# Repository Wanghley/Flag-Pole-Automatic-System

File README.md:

<!-- Improved compatibility of back to top link: See: https://github.com/othneildrew/Best-README-Template/pull/73 -->

<!--
*** Thanks for checking out the Best-README-Template. If you have a suggestion
*** that would make this better, please fork the repo and create a pull request
*** or simply open an issue with the tag "enhancement".
*** Don't forget to give the project a star!
*** Thanks again! Now go create something AMAZING! :D
-->

<!-- PROJECT SHIELDS -->
<!--
*** I'm using markdown "reference style" links for readability.
*** Reference links are enclosed in brackets [ ] instead of parentheses ( ).
*** See the bottom of this document for the declaration of the reference variables
*** for contributors-url, forks-url, etc. This is an optional, concise syntax you may use.
*** https://www.markdownguide.org/basic-syntax/#reference-style-links
-->
[![Contributors][contributors-shield]][contributors-url]
[![Forks][forks-shield]][forks-url]
[![Stargazers][stars-shield]][stars-url]
[![Issues][issues-shield]][issues-url]
[![MIT License][license-shield]][license-url]
[![LinkedIn][linkedin-shield]][linkedin-url]

<!-- PROJECT LOGO -->
<br />
<div align="center">

  <h3 align="center">Remotely Controlled Flag-Hoisting Device</h3>

  <p align="center">
    Revolutionizing the way any institution hoists its flags! Our team of aspirant engineers at the Duke Pratt School of Engineering have designed a cutting-edge, remotely controlled flag-raising system that eliminates the need for manual labor and reduces costs for the university. With our innovative technology, flag heights can be adjusted safely and easily from any location with Wi-Fi access, making it a reliable and affordable solution. Say goodbye to labor costs and health risks associated with manual flag hoisting and hello to efficient and automated flag-raising with our state-of-the-art system!
    <br />
    <a href="https://github.com/Wanghley/Flag-Pole-Automatic-System"><strong>Explore the docs »</strong></a>
    <br />
    <br />
    <a href="https://github.com/Wanghley/Flag-Pole-Automatic-System">View Demo</a>
    ·
    <a href="https://github.com/Wanghley/Flag-Pole-Automatic-System/issues">Report Bug</a>
    ·
    <a href="https://github.com/Wanghley/Flag-Pole-Automatic-System/issues">Request Feature</a>
  </p>
</div>

<!-- TABLE OF CONTENTS -->
<details>
  <summary>Table of Contents</summary>
  <ol>
    <li>
      <a href="#about-the-project">About The Project</a>
      <ul>
        <li><a href="#built-with">Built With</a></li>
      </ul>
    </li>
    <li>
      <a href="#getting-started">Getting Started</a>
      <ul>
        <li><a href="#prerequisites">Prerequisites</a></li>
        <li><a href="#installation">Installation</a></li>
      </ul>
    </li>
    <li><a href="#usage">Usage</a></li>
    <li><a href="#roadmap">Roadmap</a></li>
    <li><a href="#contributing">Contributing</a></li>
    <li><a href="#license">License</a></li>
    <li><a href="#contact">Contact</a></li>
    <li><a href="#acknowledgments">Acknowledgments</a></li>
  </ol>
</details>

<!-- ABOUT THE PROJECT -->
## About The Project

[![Product Name Screen Shot][product-screenshot]](https://example.com)

We built a remotely controlled, automatic, flag-hoisting device to service Duke University. Our client, Lee Clayton, a locksmithing specialist at Duke, has tasked us with creating an automatic, remotely-controlled system to more efficiently change flag heights for holidays and current events that require half-masting. When these special occasions arise, Duke currently relies on manual labor to lower or raise each flag one at a time.

This current system is suboptimal due to:

- Adverse weather conditions that prohibit access to flags
- Long walking time to all 16 flag poles around Duke’s campuses
- Each trip costs Duke $250 dollars, totaling to over $50,000 in the last decade.
- At the moment, the market only has automated machines that are attached to the flagpole with no remote control, an inadequate solution for the client as someone would still need to visit each pole. Our solution allows for remote control from any location with access to Duke Wi-Fi.

<p align="right">(<a href="#readme-top">back to top</a>)</p>

### Built With

<p align="right">(<a href="#readme-top">back to top</a>)</p>

<!-- GETTING STARTED -->
## Getting Started

This is an example of how you may give instructions on setting up your project locally.
To get a local copy up and running follow these simple example steps.

### Prerequisites

This is an example of how to list things you need to use the software and how to install them.
* npm
  ```sh
  npm install npm@latest -g
  ```

### Installation

_Below is an example of how you can instruct your audience on installing and setting up your app. This template doesn't rely on any external dependencies or services._

1. Get a free API Key at [https://example.com](https://example.com)
2. Clone the repo
   ```sh
   git clone https://github.com/your_username_/Project-Name.git
   ```
3. Install NPM packages
   ```sh
   npm install
   ```
4. Enter your API in `config.js`
   ```js
   const API_KEY = 'ENTER YOUR API';
   ```

<p align="right">(<a href="#readme-top">back to top</a>)</p>

<!-- USAGE EXAMPLES -->
## Usage

Use this space to show useful examples of how a project can be used. Additional screenshots, code examples and demos work well in this space. You may also link to more resources.

_For more examples, please refer to the [Documentation](https://example.com)_

<p align="right">(<a href="#readme-top">back to top</a>)</p>

<!-- ROADMAP -->
## Roadmap

- [x] Add Changelog
- [x] Add back to top links
- [ ] Add Additional Templates w/ Examples
- [ ] Add "components" document to easily copy & paste sections of the readme
- [ ] Multi-language Support
    - [ ] Chinese
    - [ ] Spanish

See the [open issues](https://github.com/othneildrew/Best-README-Template/issues) for a full list of proposed features (and known issues).

<p align="right">(<a href="#readme-top">back to top</a>)</p>

<!-- CONTRIBUTING -->
## Contributing

Contributions are what make the open source community such an amazing place to learn, inspire, and create. Any contributions you make are **greatly appreciated**.

If you have a suggestion that would make this better, please fork the repo and create a pull request. You can also simply open an issue with the tag "enhancement".
Don't forget to give the project a star! Thanks again!

1. Fork the Project
2. Create your Feature Branch (`git checkout -b feature/AmazingFeature`)
3. Commit your Changes (`git commit -m 'Add some AmazingFeature'`)
4. Push to the Branch (`git push origin feature/AmazingFeature`)
5. Open a Pull Request

<p align="right">(<a href="#readme-top">back to top</a>)</p>

<!-- LICENSE -->
## License

Distributed under the MIT License. See `LICENSE.txt` for more information.

<p align="right">(<a href="#readme-top">back to top</a>)</p>

<!-- CONTACT -->
## Contact

Your Name - [@your_twitter](https://twitter.com/your_username) - email@example.com

Project Link: [https://github.com/your_username/repo_name](https://github.com/your_username/repo_name)

<p align="right">(<a href="#readme-top">back to top</a>)</p>

<!-- ACKNOWLEDGMENTS -->
## Acknowledgments

Use this space to list resources you find helpful and would like to give credit to. I've included a few of my favorites to kick things off!

* [Choose an Open Source License](https://choosealicense.com)
* [GitHub Emoji Cheat Sheet](https://www.webpagefx.com/tools/emoji-cheat-sheet)
* [Malven's Flexbox Cheatsheet](https://flexbox.malven.co/)
* [Malven's Grid Cheatsheet](https://grid.malven.co/)
* [Img Shields](https://shields.io)
* [GitHub Pages](https://pages.github.com)
* [Font Awesome](https://fontawesome.com)
* [React Icons](https://react-icons.github.io/react-icons/search)

<p align="right">(<a href="#readme-top">back to top</a>)</p>

<!-- MARKDOWN LINKS & IMAGES -->
<!-- https://www.markdownguide.org/basic-syntax/#reference-style-links -->
[contributors-shield]: https://img.shields.io/github/contributors/Wanghley/Flag-Pole-Automatic-System.svg?style=for-the-badge
[contributors-url]: https://github.com/Wanghley/Flag-Pole-Automatic-System/graphs/contributors
[forks-shield]: https://img.shields.io/github/forks/Wanghley/Flag-Pole-Automatic-System.svg?style=for-the-badge
[forks-url]: https://github.com/Wanghley/Flag-Pole-Automatic-System/network/members
[stars-shield]: https://img.shields.io/github/stars/Wanghley/Flag-Pole-Automatic-System.svg?style=for-the-badge
[stars-url]: https://github.com/Wanghley/Flag-Pole-Automatic-System/stargazers
[issues-shield]: https://img.shields.io/github/issues/Wanghley/Flag-Pole-Automatic-System.svg?style=for-the-badge
[issues-url]: https://github.com/Wanghley/Flag-Pole-Automatic-System/issues
[license-shield]: https://img.shields.io/github/license/Wanghley/Flag-Pole-Automatic-System.svg?style=for-the-badge
[license-url]: https://github.com/Wanghley/Flag-Pole-Automatic-System/blob/master/LICENSE.md
[linkedin-shield]: https://img.shields.io/badge/-LinkedIn-black.svg?style=for-the-badge&logo=linkedin&colorB=555
[linkedin-url]: https://linkedin.com/in/wanghley
[product-screenshot]: images/screenshot.png
[Next.js]: https://img.shields.io/badge/next.js-000000?style=for-the-badge&logo=nextdotjs&logoColor=white
[Next-url]: https://nextjs.org/
[React.js]: https://img.shields.io/badge/React-20232A?style=for-the-badge&logo=react&logoColor=61DAFB
[React-url]: https://reactjs.org/
[Vue.js]: https://img.shields.io/badge/Vue.js-35495E?style=for-the-badge&logo=vuedotjs&logoColor=4FC08D
[Vue-url]: https://vuejs.org/
[Angular.io]: https://img.shields.io/badge/Angular-DD0031?style=for-the-badge&logo=angular&logoColor=white
[Angular-url]: https://angular.io/
[Svelte.dev]: https://img.shields.io/badge/Svelte-4A4A55?style=for-the-badge&logo=svelte&logoColor=FF3E00
[Svelte-url]: https://svelte.dev/
[Laravel.com]: https://img.shields.io/badge/Laravel-FF2D20?style=for-the-badge&logo=laravel&logoColor=white
[Laravel-url]: https://laravel.com
[Bootstrap.com]: https://img.shields.io/badge/Bootstrap-563D7C?style=for-the-badge&logo=bootstrap&logoColor=white
[Bootstrap-url]: https://getbootstrap.com
[JQuery.com]: https://img.shields.io/badge/jQuery-0769AD?style=for-the-badge&logo=jquery&logoColor=white
[JQuery-url]: https://jquery.com

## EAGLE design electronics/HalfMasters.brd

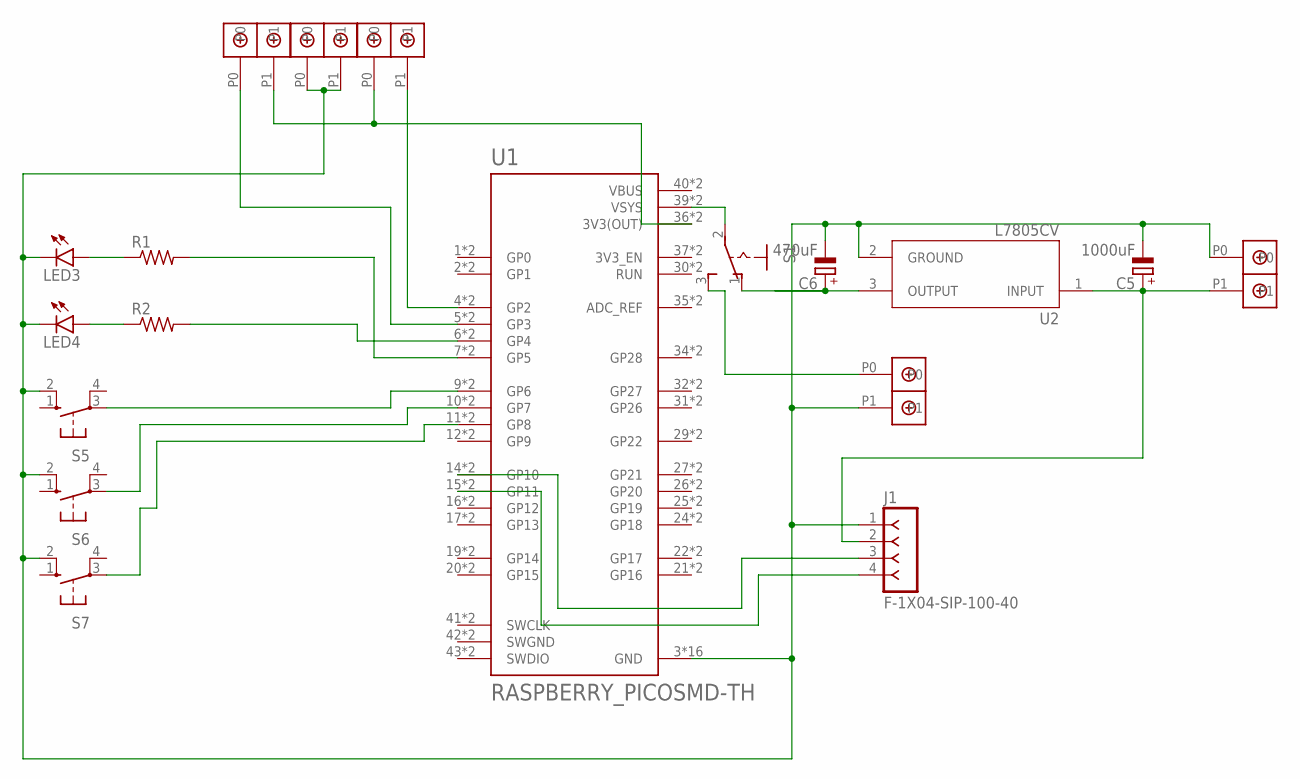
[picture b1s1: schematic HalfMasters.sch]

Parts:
C5: 1000uF; E2-5
C6: 470uF; E2-5
J1: F-1X04-SIP-100-40; SIP-100-04-40
LED3, LED4: LED5MM
R1, R2: R-US_0207/10; 0207/10
S1: 255SB
S5, S6, S7: 10-XX; B3F-10XX
U1: RASPBERRY_PICOSMD-TH; PICO-PKG
U2: L7805CV; TO255P1040X460X1968-3
U$1, U$2, U$3, U$4, U$5: DBCONN-1X2

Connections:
unnamed: R2.2, U1.6 (GP4), U1.P$6 (GP4)
unnamed: R1.2, U1.7 (GP5), U1.P$7 (GP5)
unnamed: S1.3 (S), U$5.P0
unnamed: J1.3, U1.14 (GP10), U1.P$14 (GP10)
unnamed: J1.4, U1.15 (GP11), U1.P$15 (GP11)
unnamed: S1.2, U1.39 (VSYS), U1.P$39 (VSYS)
unnamed: C6.+, S1.1 (O), U2.3 (OUTPUT)
unnamed: U1.36 (3V3(OUT)), U1.P$36 (3V3(OUT)), U$1.P1, U$3.P0
unnamed: U1.4 (GP2), U1.P$4 (GP2), U$3.P1
unnamed: U1.5 (GP3), U1.P$5 (GP3), U$1.P0
unnamed: LED3.A, R1.1
unnamed: LED4.A, R2.1
unnamed: C5.+, J1.2, U2.1 (INPUT), U$4.P1
unnamed: C5.-, C6.-, J1.1, LED3.K (C), LED4.K (C), S5.2 (S1), S6.2 (S1), S7.2 (S1), U1.3 (GND), U1.8 (GND), U1.13 (GND), U1.18 (GND), U1.23 (GND), U1.28 (GND), U1.33 (GND), U1.38 (GND), U1.P$3 (GND), U1.P$8 (GND), U1.P$13 (GND), U1.P$18 (GND), U1.P$23 (GND), U1.P$28 (GND), U1.P$33 (GND), U1.P$38 (GND), U2.2 (GROUND), U$2.P0, U$2.P1, U$4.P0, U$5.P1
unnamed: S5.3, U1.9 (GP6), U1.P$9 (GP6)
unnamed: S6.3, U1.10 (GP7), U1.P$10 (GP7)
unnamed: S7.3, U1.11 (GP8), U1.P$11 (GP8)
SWGND: U1.42 (SWGND), U1.P$42 (SWGND)
VBUS: U1.40 (VBUS), U1.P$40 (VBUS)

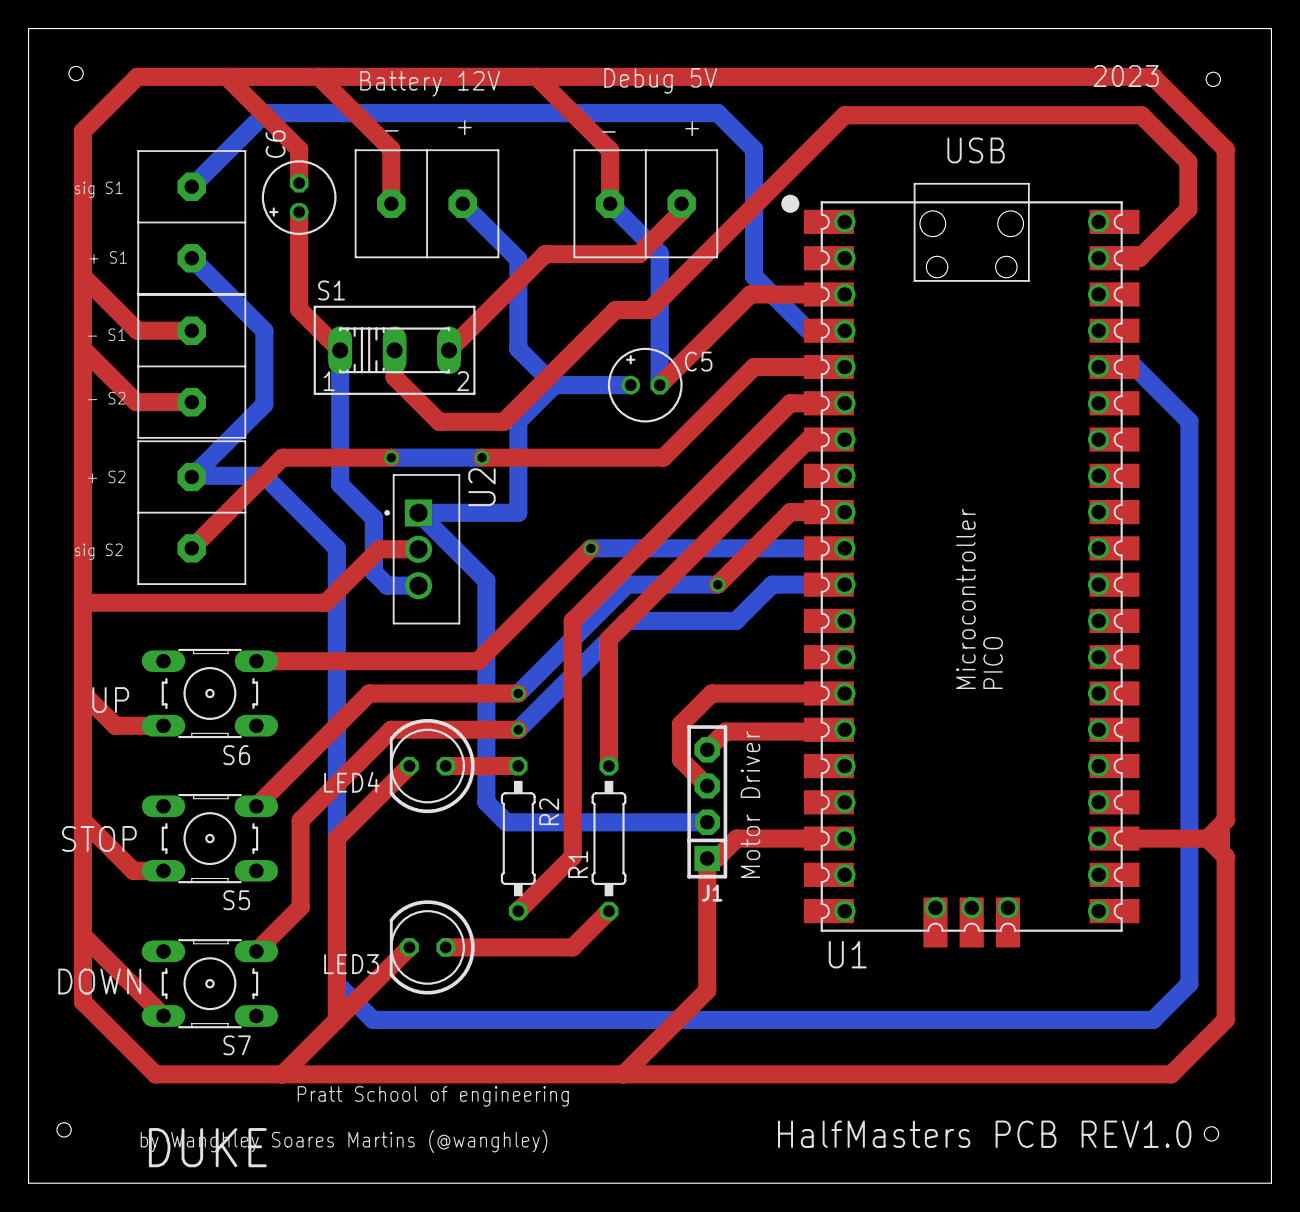
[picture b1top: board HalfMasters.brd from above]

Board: 2 copper layers, 87.0 x 80.8 mm, 18 parts (0 on the bottom side), 19 nets.

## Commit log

2022-10-19 feat: initial work on README for flagpole project
    Add initial template to work on for the flag pole project
2022-10-19 feat: functional firmware for prototype using angular movement
2022-10-24 feat: insert automatic command to set up and down
2022-10-24 feat: full control of motion of the device
    TODO: needs to implement saving on EEPROM and set up remote control by IP address
2022-10-26 fix!: correct movement from top position to middle position
    Wrong movement command on moving from up to middle corrected
2022-10-26 fix: remove non-used variables
    remove variables not used in the context what of problem
2022-10-26 feat!: implements EEPROM storage and data recovery
    Implements writting and reading on the EEPROM
2022-11-16 fix!: operational microcontroller kit functional w serial communication
    implemented communication to be received from nodemcu through wireless
2022-11-16 feat: nodeMCU ESP8266 rest API functional code + serial comm
    Implements ESP8266 rest API w/ Serial communication to microcontroller
2022-11-21 feat: implementation NEMA 23 + AccelStepper
    Implement AccelStepper library v1.61.0
    Default setings for NEMA 23 motor driver
    TB6600
2023-01-28 commit1
2023-01-28 refactor: move website and api code to web folder
2023-02-12 feat: initial code developed for pico W implementation
2023-02-12 feat: implementation with microdot
    add initial page
    add initial work on go up and down
    implement async webserver
2023-02-12 feat: add more information to / page
2023-02-16 feat: initial addiction of libraries and electronics folder to repository
2023-03-20 feat: libraries for new components of motor drive added
2023-03-20 feat: electronics libraries added
2023-03-20 feat: initial functional code with pico platform
    functional code with basic implementation on the raspberry pi
    Only one hall effect sensor added
2023-03-20 feat: database schema and design
    first draw of the database for the project
2023-03-20 feat: initial work on SQL for the database - written based on the schema
2023-03-22 fix!: add cardinality to MER diagram
    DB version one ready to be programmed and deployed to website.
2023-03-23 feat: final rev 1 schematic of controller circuit
2023-03-23 feat: rev 1 of the PCB designed ready
2023-03-23 refactor: logo for PCB
2023-03-23 refactor: schematic needed libraries
2023-03-23 fix: add correct attributes and mapping
2023-03-24 fix: change vias width to match Duke requirements
2023-03-24 refactor: remove backspace from the end of the bmp filename
2023-03-24 refactor: removing unecessary file
2023-03-24 refactor: remove old bmp filename
2023-03-25 feat: implement function to go down once command is received by HTTP POST
2023-03-31 fix: 7805 position inverted vertically
    No problem on the design, but this change will allow the voltage regulator to be placed bend in the PCB
2023-04-01 feat: add title and summary
2023-04-01 feat: introduction and built with
2023-04-01 feat: built with in single line
2023-04-02 fix: add correct badge links
2023-04-02 fix!: correct badge links
2023-04-02 feat: license CC BY-NC-SA 4.0 added
2023-04-02 fix: lincese link badge
2023-04-02 fix: add license name in the beginning
2023-04-02 fix: add logo based on AI
2023-04-02 feat: insert docs to repository
2023-04-02 fix: correcting hyperlinks on header
2026-01-17 refacotr: code upload to github

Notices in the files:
parts and their libraries:
con-headers-jp: Copyright (C) 2008, Bob Starr
